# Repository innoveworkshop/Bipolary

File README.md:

# Bipolary

A minimalist discrete desktop class-A headphone amplifier.

## Follow Along

If you want to learn more about this project and also follow along its journey,
check out the [project's YouTube playlist](https://www.youtube.com/playlist?list=PLbjMhZ3Qv6a8xDwKZuQG69gMUy-2NGEBN).

## Component Library

In order to keep my projects 100% consistent I've built my own Eagle library,
which is all standardized and nice. So if you want to hack on this project be
sure to download the [Innove Workshop Eagle library](https://github.com/innoveworkshop/InnoveWorkshop-Eagle-Library).

## License

<br />This work is licensed under a <a rel="license" href="http://creativecommons.org/licenses/by-nc-sa/4.0/">Creative Commons Attribution-NonCommercial-ShareAlike 4.0 International License</a>.

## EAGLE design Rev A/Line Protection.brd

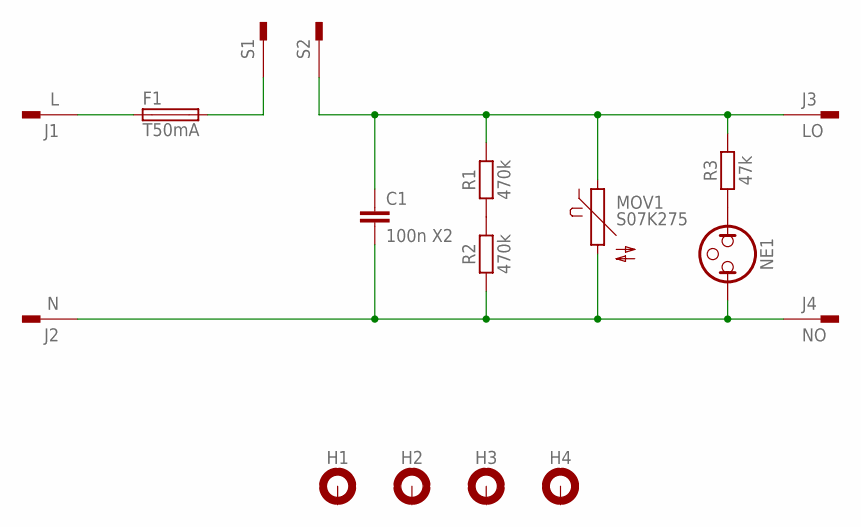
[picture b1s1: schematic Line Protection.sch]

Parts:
C1: 100n X2; C150-054X183
F1: T50mA; CFH14
H1, H2, H3, H4: MOUNT-PAD-ROUND3.0; 3,0-PAD
J1: L; F061.100
J2: N; F061.100
J3: LO; F061.100
J4: NO; F061.100
MOV1: S07K275
NE1: NEON-T2
R1, R2: 470k; 0207/10
R3: 47k; 0207/10
S1, S2: FASTON-250D140; F061.100

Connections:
unnamed: F1.1, J1.A1, J1.A2
unnamed: R1.1, R2.2
unnamed: NE1.1, R3.1
unnamed: F1.2, S1.A1, S1.A2
NEUTRAL: C1.2, J2.A1, J2.A2, J4.A1, J4.A2, MOV1.2, NE1.2, R2.1
SLIVE: C1.1, J3.A1, J3.A2, MOV1.1, R1.2, R3.2, S2.A1, S2.A2

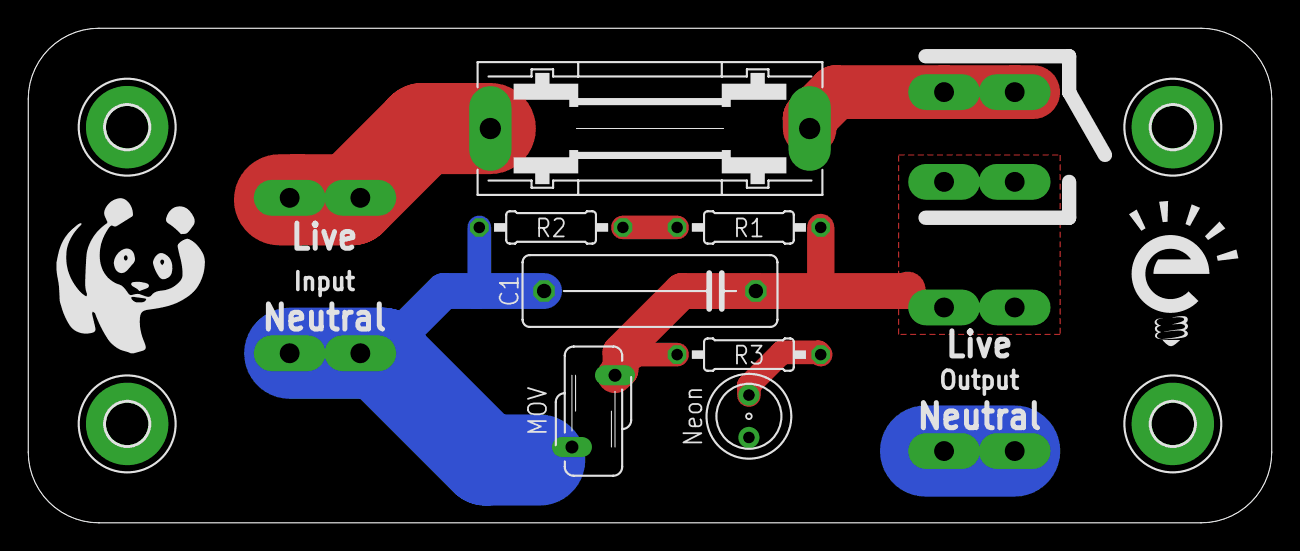
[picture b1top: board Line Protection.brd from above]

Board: 2 copper layers, 88.0 x 35.0 mm, 17 parts (0 on the bottom side), 6 nets.

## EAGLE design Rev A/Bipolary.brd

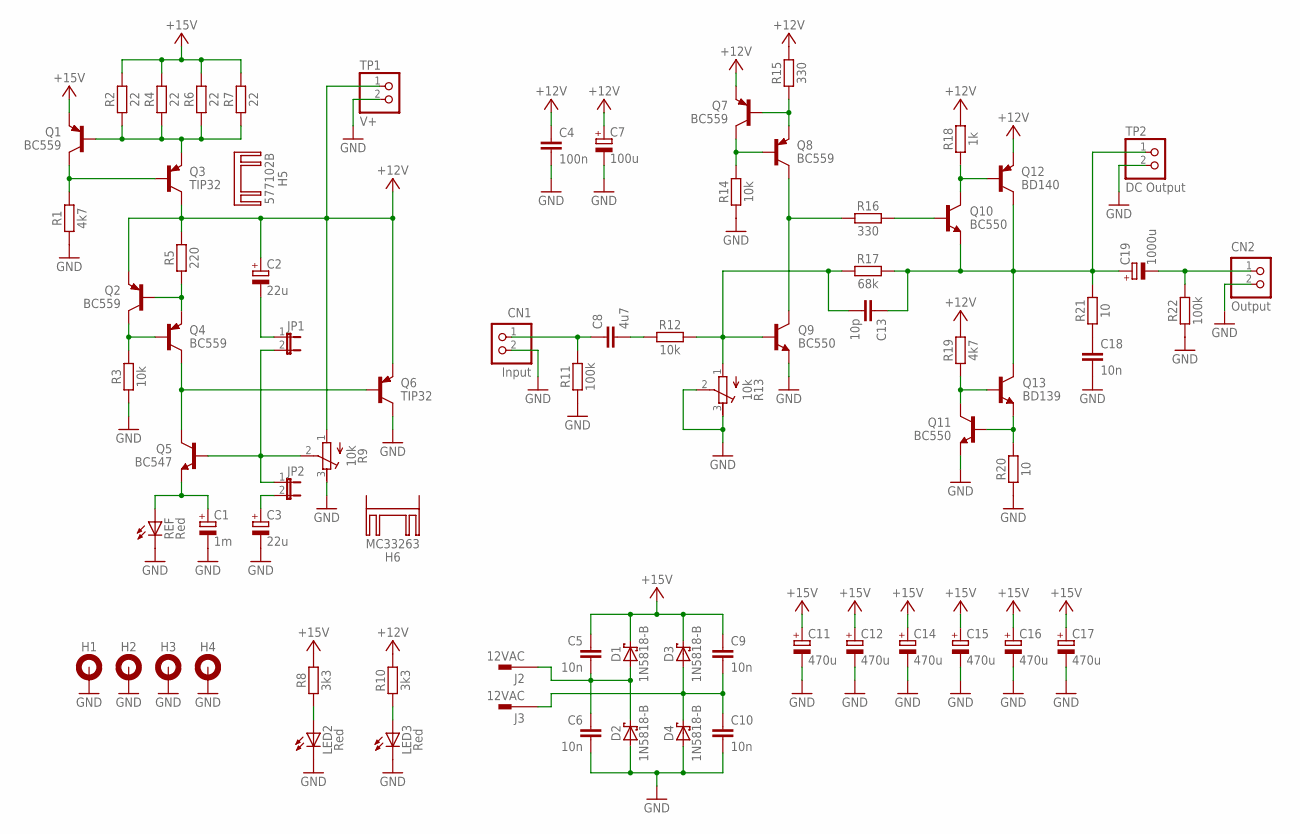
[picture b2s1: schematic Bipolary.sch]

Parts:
C1: 1m; E3,5-8
C2, C3: 22u; E2-5
C4: 100n; C050-025X075
C5, C6, C9, C10, C18: 10n; C050-025X075
C7: 100u; E3,5-8
C8: 4u7; C150-084X183
C11, C12, C14, C15, C16, C17: 470u; E5-10
C13: 10p; C050-025X075
C19: 1000u; E5-10
CN1: Input; B2B-XH-A
CN2: Output; B2B-XH-A
D1, D2, D3, D4: 1N5818-B; DO41-7.6
H1, H2, H3, H4: MOUNT-PAD-ROUND3.0; 3,0-PAD
H5: 577102B; D02S
H6: MC33263; SK104-PAD
J2, J3: 12VAC; F061.100
JP1, JP2: JP1E; JP1
LED2, LED3: Red; LED5MM
Q1, Q2, Q4, Q7, Q8: BC559; TO92
Q3, Q6: TIP32; TO220V
Q5: BC547; TO92
Q9, Q10, Q11: BC550; TO92
Q12: BD140; TO126V
Q13: BD139; TO126V
R1, R19: 4k7; 0207/10
R2, R4, R6, R7: 22; 0207/10
R3, R12, R14: 10k; 0207/10
R5: 220; 0207/10
R8, R10: 3k3; 0207/10
R9, R13: 10k; RTRIM3296Y
R11, R22: 100k; 0207/10
R15, R16: 330; 0207/10
R17: 68k; 0207/10
R18: 1k; 0207/10
R20, R21: 10; 0207/10
REF: Red; LED5MM
TP1: V+; 1X02
TP2: DC Output; 1X02

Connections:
+12V: C2.+, C4.1, C7.+, Q2.3 (E), Q3.2 (C), Q6.3 (E), Q7.3 (E), Q12.1 (E), R5.2, R9.1 (A), R10.2, R15.2, R18.2, R19.2, TP1.1
+15V: C5.1, C9.1, C11.+, C12.+, C14.+, C15.+, C16.+, C17.+, D1.C, D3.C, Q1.3 (E), R2.2, R4.2, R6.2, R7.2, R8.2
DCOUTPUT: C13.1, C19.+, Q10.3 (E), Q12.2 (C), Q13.2 (C), R17.2, R21.2, TP2.1
GND: C1.-, C3.-, C4.2, C6.2, C7.-, C10.2, C11.-, C12.-, C14.-, C15.-, C16.-, C17.-, C18.2, CN1.2, CN2.2, D2.A, D4.A, H1.B3,0, H2.B3,0, H3.B3,0, H4.B3,0, LED2.K (C), LED3.K (C), Q6.2 (C), Q9.3 (E), Q11.3 (E), R1.1, R3.1, R9.3 (E), R11.1, R13.2 (S), R13.3 (E), R14.1, R20.1, R22.1, REF.K (C), TP1.2, TP2.2
INPUT: C8.1, CN1.1, R11.2
INTSTAGE: Q8.1 (C), Q9.1 (C), R16.1
unnamed: Q1.1 (C), Q3.1 (B), R1.2
unnamed: C8.2, R12.1
unnamed: C5.2, C6.1, D1.A, D2.C, J2.A1, J2.A2
unnamed: Q7.1 (C), Q8.2 (B), R14.2
unnamed: Q7.2 (B), Q8.3 (E), R15.1
unnamed: Q10.1 (C), Q12.3 (B), R18.1
unnamed: Q10.2 (B), R16.2
unnamed: Q11.1 (C), Q13.3 (B), R19.1
unnamed: Q11.2 (B), Q13.1 (E), R20.2
unnamed: C18.1, R21.1
unnamed: Q1.2 (B), Q3.3 (E), R2.1, R4.1, R6.1, R7.1
unnamed: Q2.2 (B), Q4.3 (E), R5.1
unnamed: Q2.1 (C), Q4.2 (B), R3.2
unnamed: Q4.1 (C), Q5.1 (C), Q6.1 (B)
unnamed: C1.+, Q5.3 (E), REF.A
unnamed: JP1.2, JP2.1, Q5.2 (B), R9.2 (S)
unnamed: C2.-, JP1.1
unnamed: C3.+, JP2.2
unnamed: C9.2, C10.1, D3.A, D4.C, J3.A1, J3.A2
unnamed: LED3.A, R10.1
unnamed: LED2.A, R8.1
NFB: C13.2, Q9.2 (B), R12.2, R13.1 (A), R17.1
OUTPUT: C19.-, CN2.1, R22.2

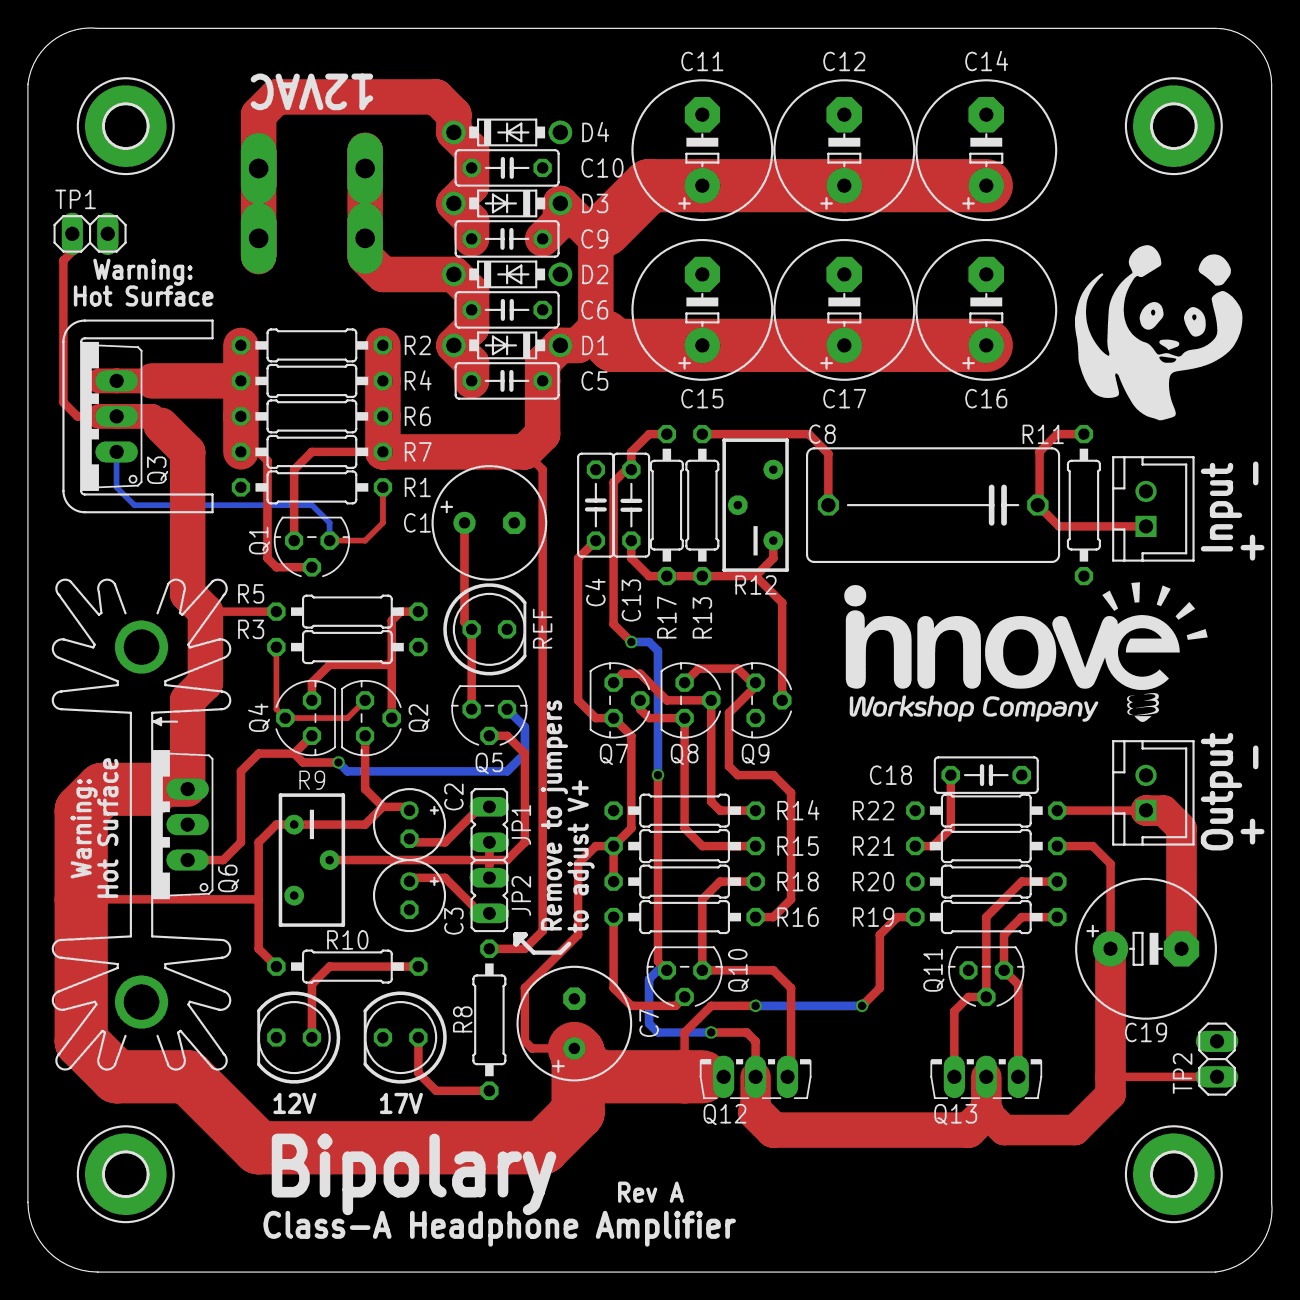
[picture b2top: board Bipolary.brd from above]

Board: 2 copper layers, 89.0 x 89.0 mm, 75 parts (0 on the bottom side), 29 nets.

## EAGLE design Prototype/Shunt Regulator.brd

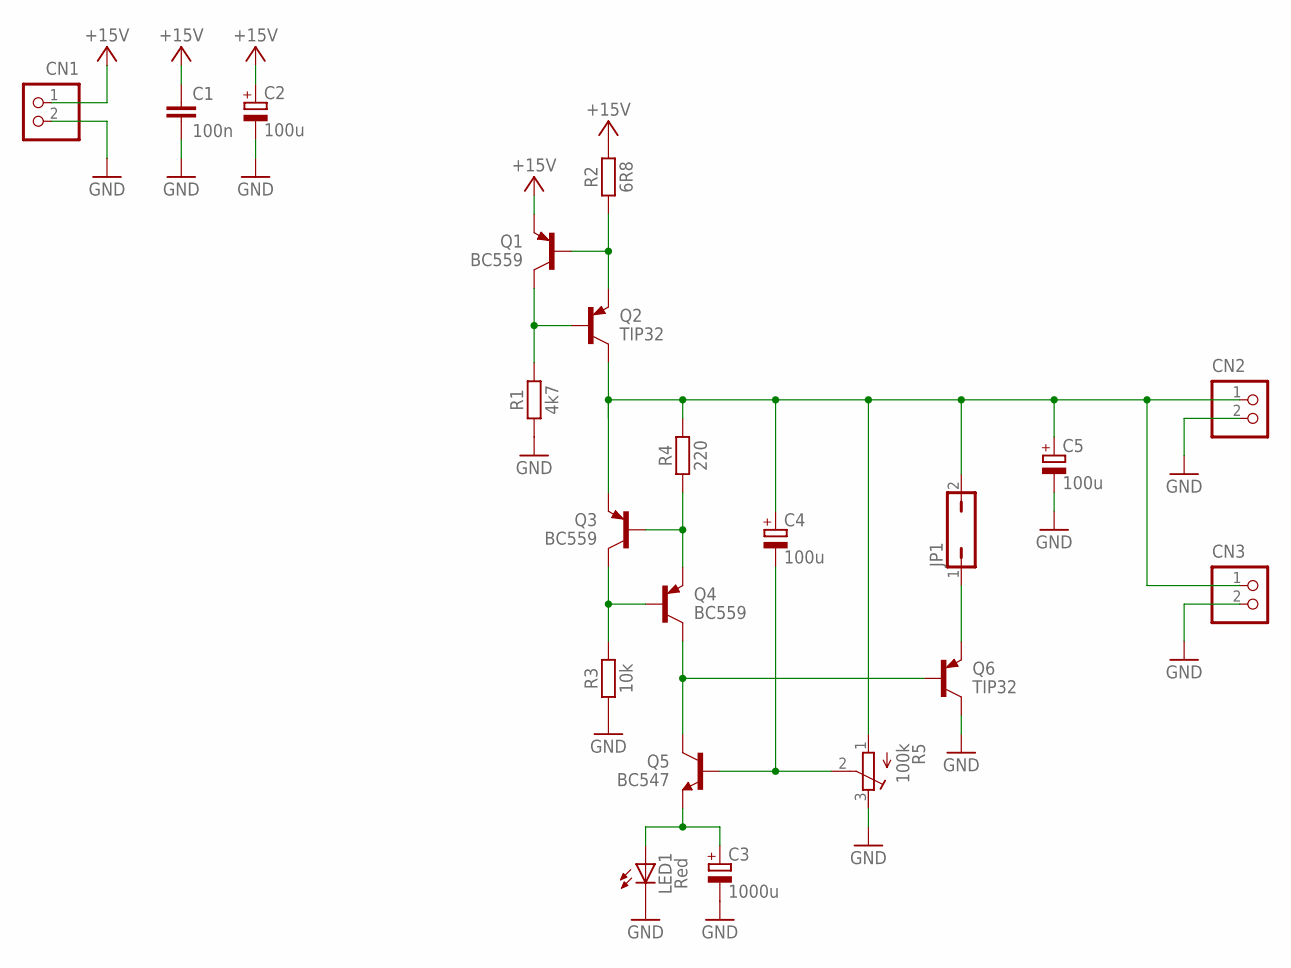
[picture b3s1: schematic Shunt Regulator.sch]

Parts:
C1: 100n; C050-025X075
C2, C4, C5: 100u; E2,5-6
C3: 1000u; E5-10
CN1, CN2, CN3: B2B-XH-A
JP1: JP1Q; JP1
LED1: Red; LED5MM
Q1, Q3, Q4: BC559; TO92
Q2, Q6: TIP32; TO220V
Q5: BC547; TO92
R1: 4k7; 0207/10
R2: 6R8; 0207/10
R3: 10k; 0207/10
R4: 220; 0207/10
R5: 100k; RTRIM3296Y

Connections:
+15V: C1.1, C2.+, CN1.1, Q1.3 (E), R2.2
GND: C1.2, C2.-, C3.-, C5.-, CN1.2, CN2.2, CN3.2, LED1.K (C), Q6.2 (C), R1.1, R3.1, R5.3 (E)
unnamed: Q1.1 (C), Q2.1 (B), R1.2
unnamed: Q1.2 (B), Q2.3 (E), R2.1
unnamed: Q4.1 (C), Q5.1 (C), Q6.1 (B)
unnamed: Q3.2 (B), Q4.3 (E), R4.1
unnamed: Q3.1 (C), Q4.2 (B), R3.2
unnamed: C3.+, LED1.A, Q5.3 (E)
unnamed: C4.-, Q5.2 (B), R5.2 (S)
unnamed: JP1.1, Q6.3 (E)
OUTPUT: C4.+, C5.+, CN2.1, CN3.1, JP1.2, Q2.2 (C), Q3.3 (E), R4.2, R5.1 (A)

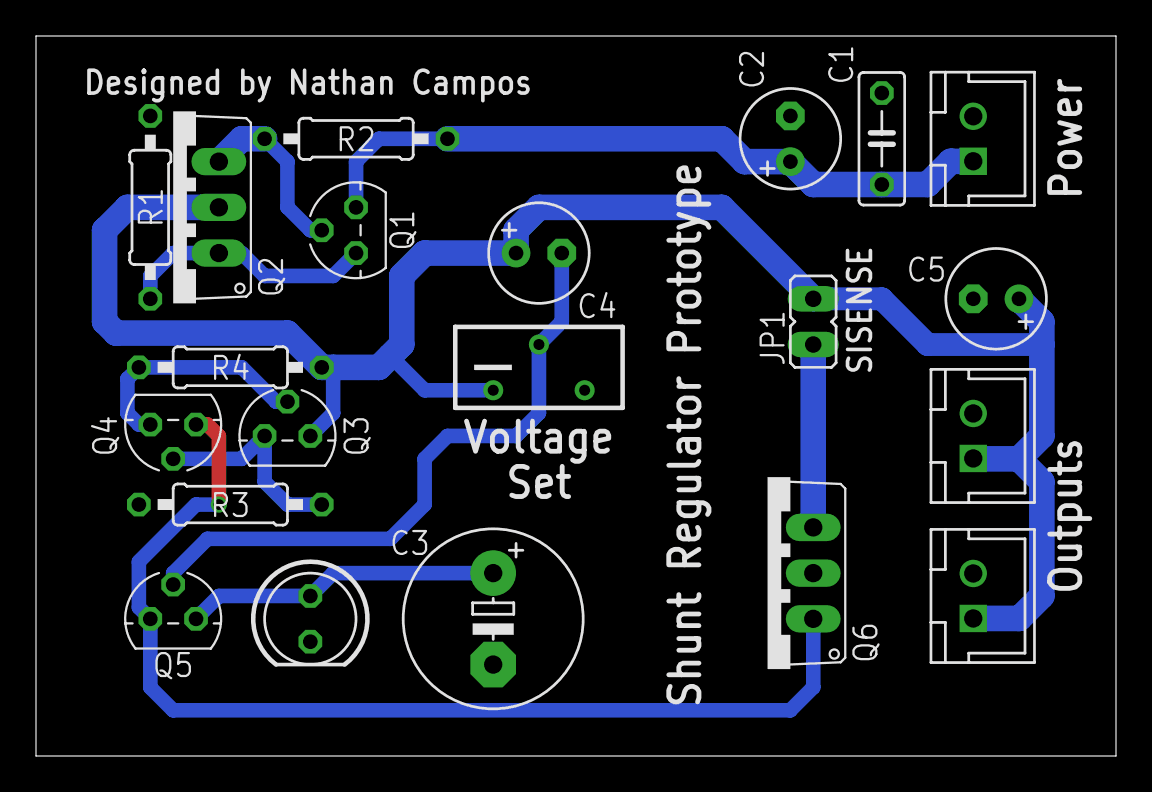
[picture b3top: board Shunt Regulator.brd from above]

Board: 2 copper layers, 60.0 x 40.0 mm, 21 parts (0 on the bottom side), 11 nets.

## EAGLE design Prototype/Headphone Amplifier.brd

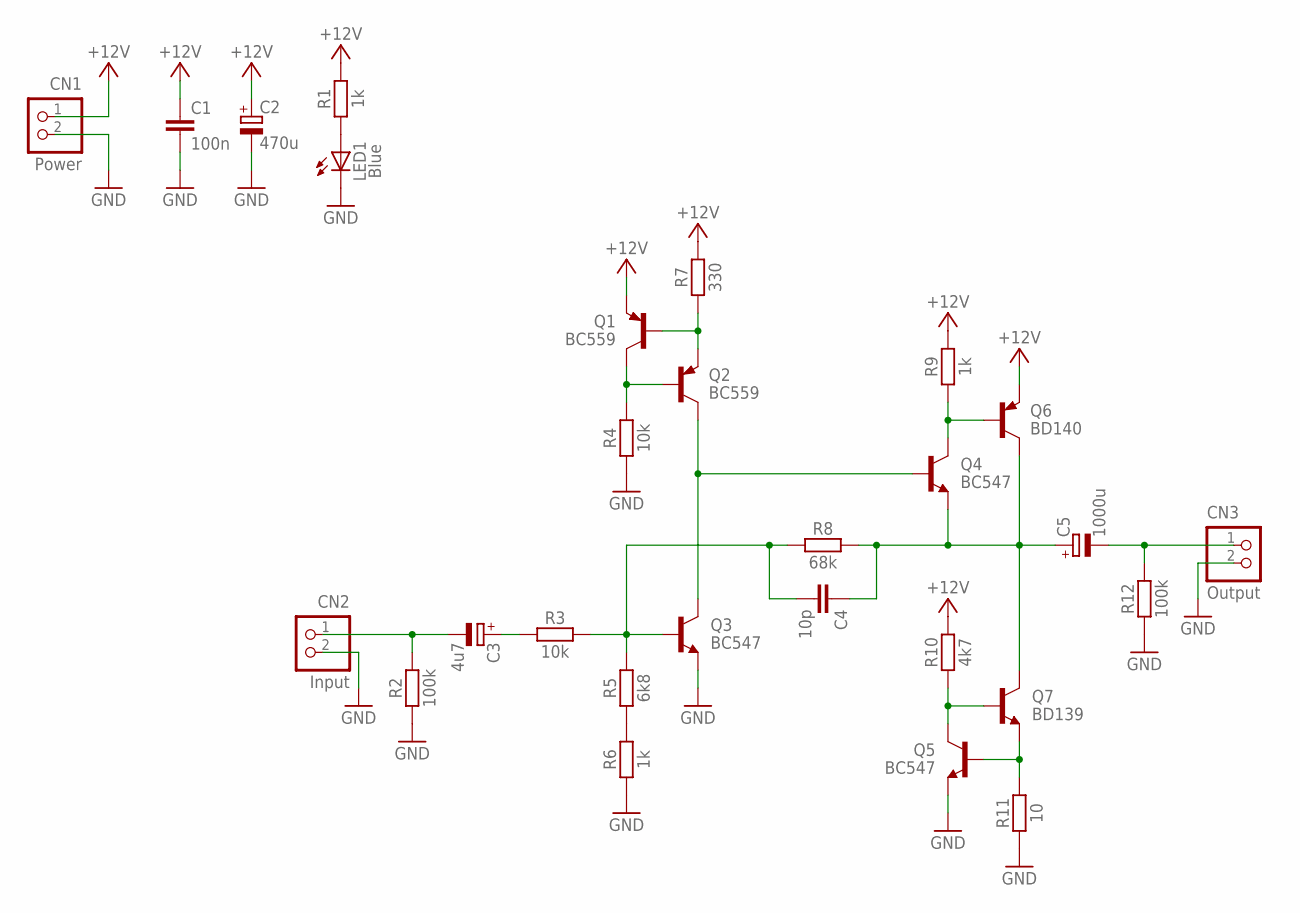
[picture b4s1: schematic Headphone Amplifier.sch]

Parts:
C1: 100n; C050-025X075
C2: 470u; E5-10
C3: 4u7; E1,8-4
C4: 10p; C050-025X075
C5: 1000u; E5-10
CN1: Power; B2B-XH-A
CN2: Input; B2B-XH-A
CN3: Output; B2B-XH-A
LED1: Blue; LED5MM
Q1, Q2: BC559; TO92
Q3, Q4, Q5: BC547; TO92
Q6: BD140; TO126V
Q7: BD139; TO126V
R1, R6, R9: 1k; 0207/10
R2, R12: 100k; 0207/10
R3, R4: 10k; 0207/10
R5: 6k8; 0207/10
R7: 330; 0207/10
R8: 68k; 0207/10
R10: 4k7; 0207/10
R11: 10; 0207/10

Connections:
+12V: C1.1, C2.+, CN1.1, Q1.3 (E), Q6.1 (E), R1.2, R7.2, R9.2, R10.2
DCOUTPUT: C4.1, C5.+, Q4.3 (E), Q6.2 (C), Q7.2 (C), R8.2
GND: C1.2, C2.-, CN1.2, CN2.2, CN3.2, LED1.K (C), Q3.3 (E), Q5.3 (E), R2.1, R4.1, R6.1, R11.1, R12.1
INPUT: C3.-, CN2.1, R2.2
INTSTAGE: Q2.1 (C), Q3.1 (C), Q4.2 (B)
unnamed: R5.1, R6.2
unnamed: C3.+, R3.1
unnamed: LED1.A, R1.1
unnamed: Q1.1 (C), Q2.2 (B), R4.2
unnamed: Q1.2 (B), Q2.3 (E), R7.1
unnamed: Q4.1 (C), Q6.3 (B), R9.1
unnamed: Q5.1 (C), Q7.3 (B), R10.1
unnamed: Q5.2 (B), Q7.1 (E), R11.2
NFB: C4.2, Q3.2 (B), R3.2, R5.2, R8.1
OUTPUT: C5.-, CN3.1, R12.2

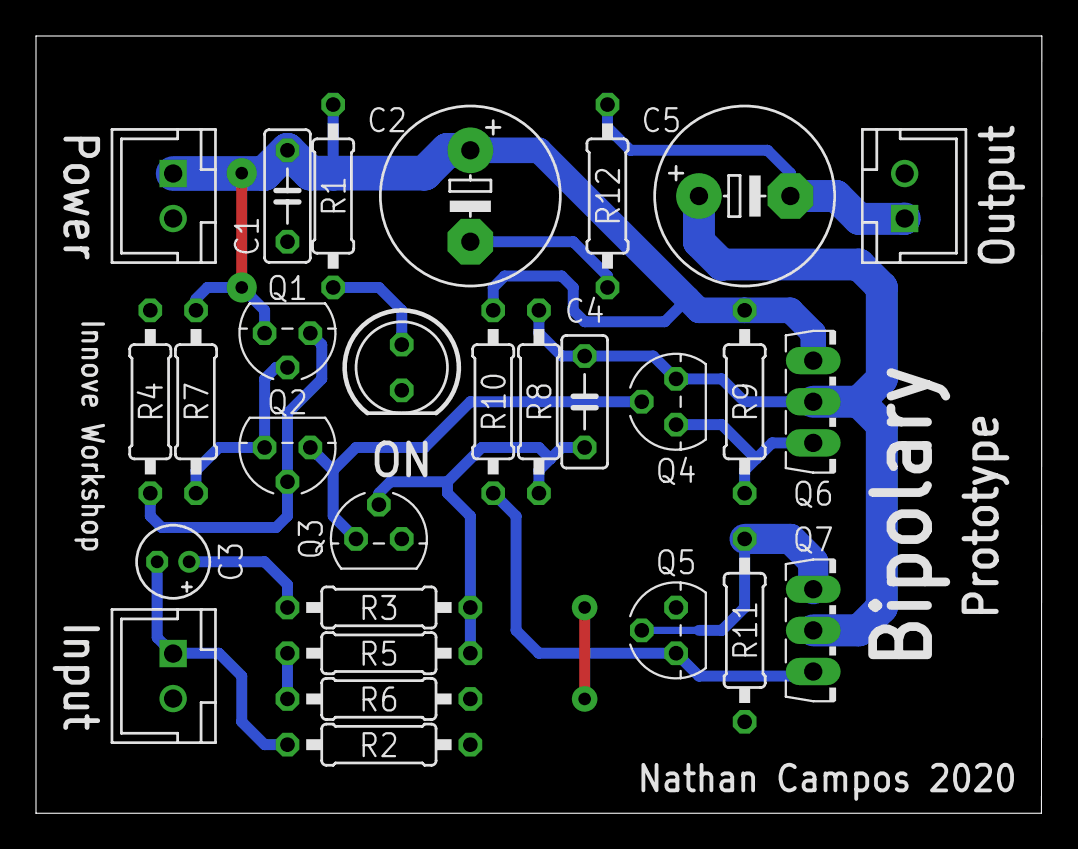
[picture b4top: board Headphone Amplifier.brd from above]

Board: 2 copper layers, 55.9 x 43.2 mm, 28 parts (0 on the bottom side), 15 nets.

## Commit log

2020-09-20 Added simulations
2020-09-20 Added EAGLE files
2020-09-20 Set the project name
2020-09-20 Renumbered the reference designators in the schematic
2020-09-21 Prototype circuit done
2020-09-21 Friendly library reminder
2020-09-21 Added the oscillation containment components to the simulation
2020-09-21 Minor typo
2020-09-21 Added some simulations for older videos
2020-09-22 Using the Innove BJT library
2020-09-29 Mitigating oscillations
2020-09-29 Started working on the shunt regulator
2020-09-30 Doing some stability simulations on the regulator
2020-09-30 Finished the shunt regulator prototype
2020-10-14 Added Rev A schematic and board layout
2020-10-14 Minor tweaks
2020-10-14 Finished the line protection schematic and board layout
2020-11-30 Added AutoCAD files to the ignore list
2020-11-30 Started a blank AutoCAD drawing for the enclosure
2020-11-30 Determined the relative position of the transformer and boards
2020-11-30 CAD - Placed spacers and positioned everything vertically
2020-12-01 CAD - Positioned the boards in their final location and placed the sheet metal base, front and back
2020-12-01 CAD - Finalized the size of the enclosure after some paper fitting
2020-12-01 CAD - Added the front panel holes and added the switch and neon indicator
2020-12-01 CAD - Made all the holes for screws in the sheet metal base
2020-12-01 CAD - Added the 1/4 inch jack to the front panel
2020-12-02 CAD - Finished placing all the back panel components
2020-12-02 CAD - Added the back RCA input jacks I forgot
2020-12-02 CAD - Finished the 3D model of the bottom plate
2020-12-02 CAD - Laid out a flat pattern
2020-12-03 CAD - Finished the base flat pattern
2020-12-03 CAD - Added side faces to the 3D model
2020-12-03 CAD - Renamed the base plate flat pattern drawing
2020-12-03 CAD - Added the flat pattern for the side plates
2020-12-03 CAD - Added the top plate to the 3D model
2020-12-03 CAD - Just making sure the side plate flat pattern was saved using the R14 format
2020-12-03 CAD - Finished the top plate flat pattern
2020-12-21 Fixed something on the side plates flat pattern. Can't remember
2020-12-21 Updated all the CAD drawings with layouts for printing
2021-04-02 Added more files to the gitignore
2021-04-02 Added some measurements from the final project
2021-04-02 Started working on plotting some of the measurements
2021-04-02 Plotting frequency response
2021-04-02 Ignoring .RData files
2021-04-02 Removed the output level graph
